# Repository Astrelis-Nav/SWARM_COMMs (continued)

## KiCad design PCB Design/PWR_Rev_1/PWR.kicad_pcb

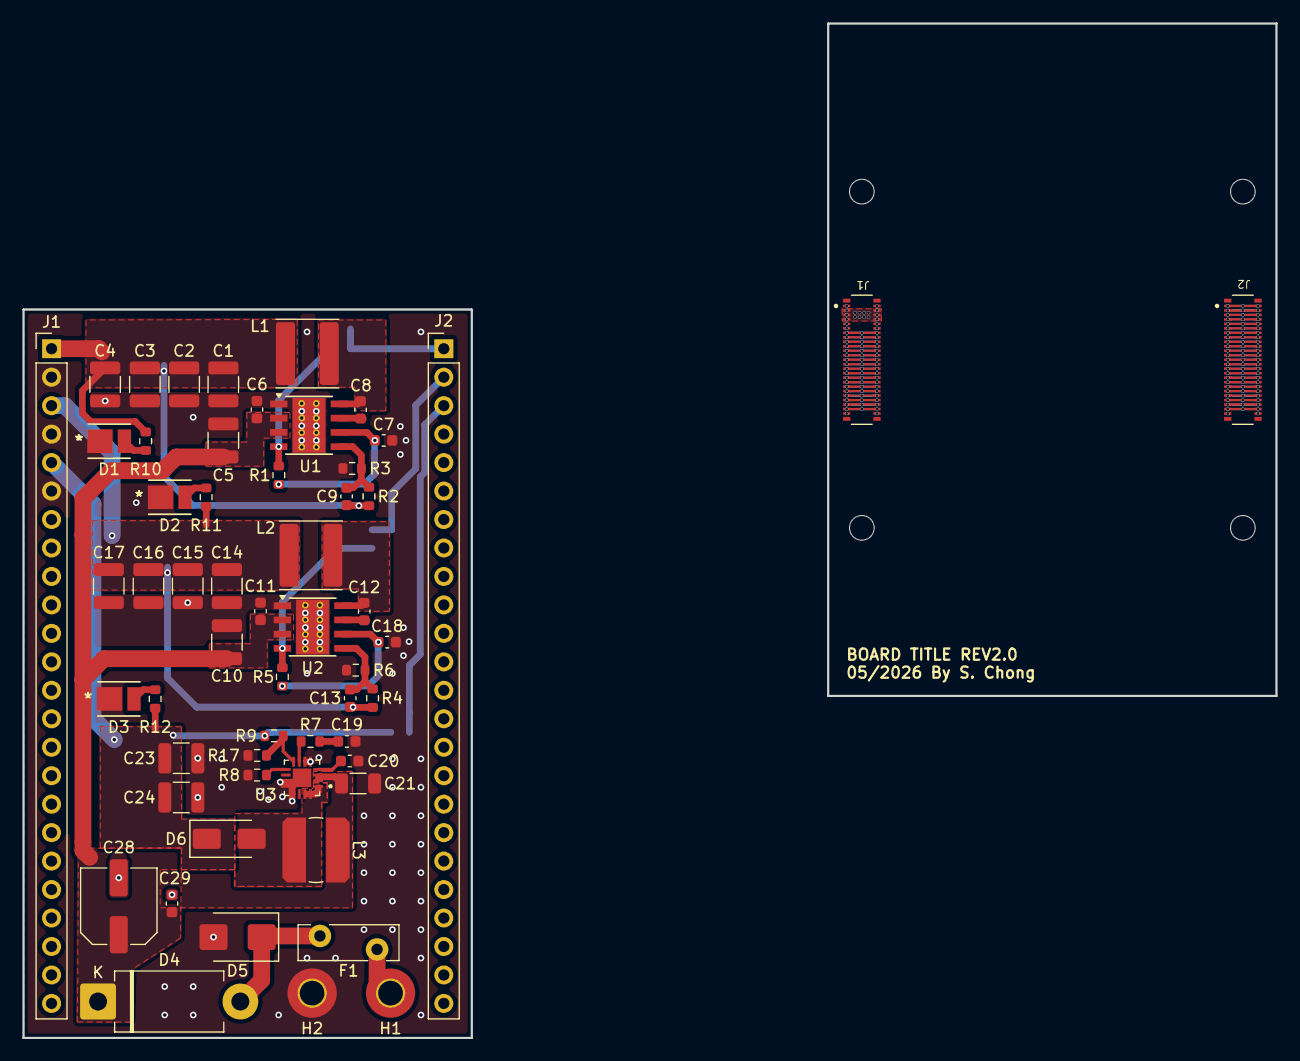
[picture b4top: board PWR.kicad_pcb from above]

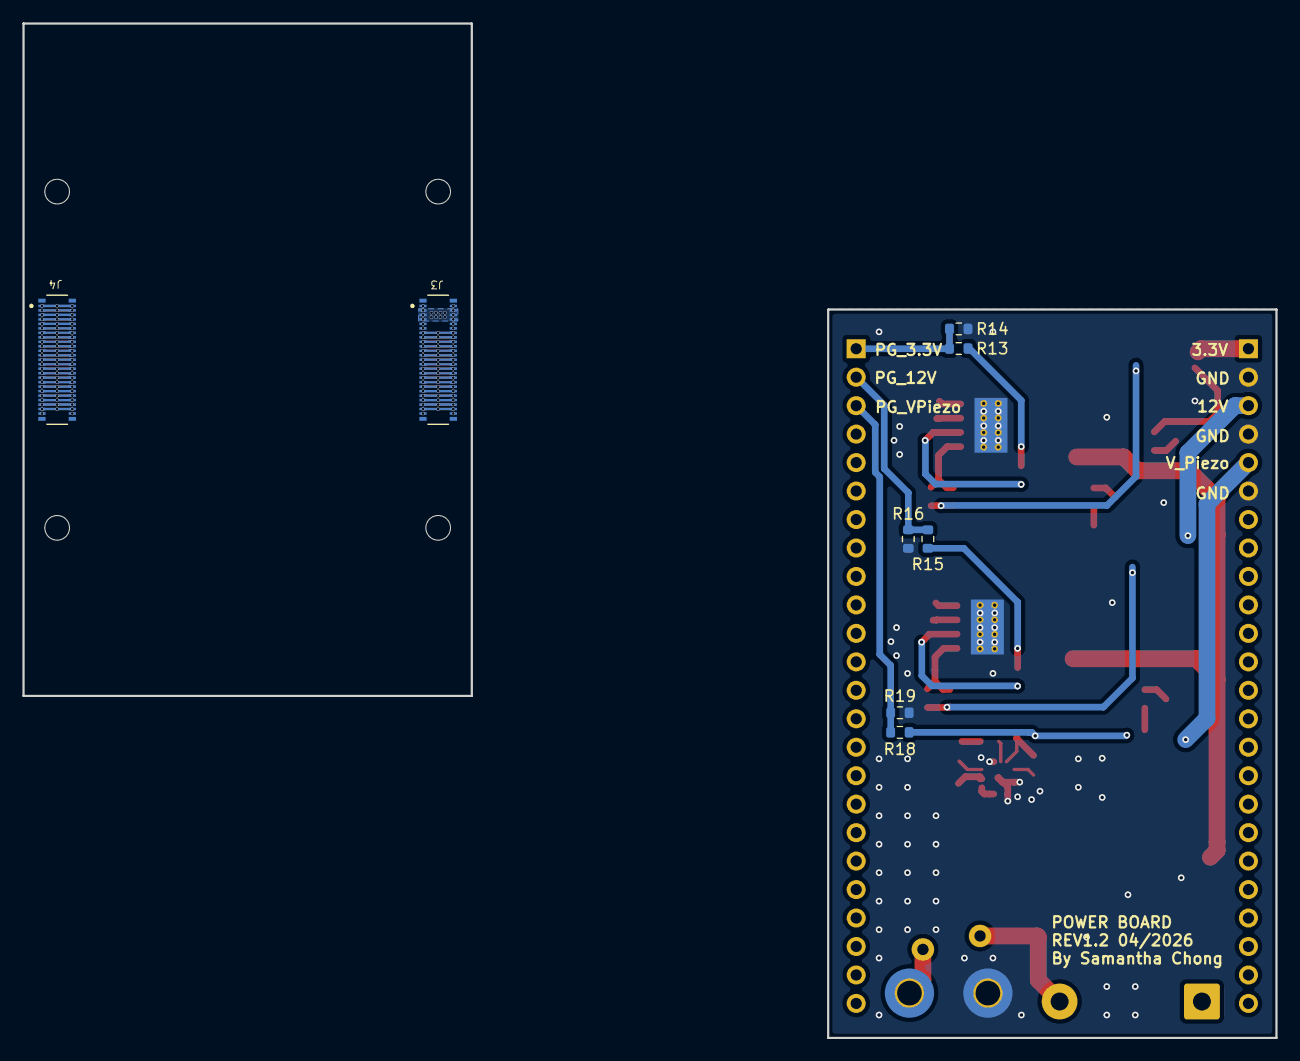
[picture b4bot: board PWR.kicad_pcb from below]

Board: 2 copper layers, 40.0 x 65.0 mm, 65 parts (8 on the bottom side), 71 nets.

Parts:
C1, C2, C3, C4, C14, C15, C16, C17, C23, C24: 22u; C_1210_3225Metric
C5, C10: 10u; C_1210_3225Metric
C6, C11: 0.22u; C_0603_1608Metric
C7, C18: 1u; C_0603_1608Metric
C8, C12: 0.1u; C_0603_1608Metric
C9, C13: C; C_0603_1608Metric
C19: 10n; C_0603_1608Metric
C20: 100n; C_0603_1608Metric
C21: 10u; C_1206_3216Metric
C28: 100uF; C_Elec_6.3x5.8
C29: 2.2uF; C_0603_1608Metric
D1: GREEN; LED_JE2835_CRW
D2, D3: BLUE; LED_JE2835_CRW
D4: STPS5L40; D_DO-201AD_P12.70mm_Horizontal
D5: SMBJ18A; D_SMB
D6: SS34-HF; D_SMA
F1: MF-R300; Fuse_Bourns_MF-RHT300
H1, H2: MountingHole_Pad; MountingHole_2.2mm_M2_Pad_TopBottom
J1, J2, J3, J4: Conn_02x25_Odd_Even; HIROSE_DF40C-50DP-0.4V_51_
J1#2, J2#2: Conn_01x24_Pin; PinHeader_1x24_P2.54mm_Vertical
L1: 6.8u; L_Wuerth_MAPI-5030
L2: 15u; L_Wuerth_MAPI-5030
L3: 22u; L_Bourns_SDR0604
R1, R2, R4, R5, R13, R15: 100k; R_0603_1608Metric
R3: 43.2k; R_0603_1608Metric
R6: 9.09k; R_0603_1608Metric
R7, R17, R19: 10k; R_0603_1608Metric
R8: 84.5k; R_0603_1608Metric
R9: 187k; R_0603_1608Metric
R10: 1k; R_0603_1608Metric
R11: 9.1k; R_0603_1608Metric
R12: R; R_0603_1608Metric
R14, R16: 51k; R_0603_1608Metric
R18: 182k; R_0603_1608Metric
U1, U2: LMR33630ADDA; Texas_HSOP-8-1EP_3.9x4.9mm_P1.27mm_ThermalVias
U3: TPS55340RTER; QFN50P300X300X80-17N

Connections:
3.3V: C1.1, C2.1, C3.1, C4.1, C9.1, J1.3, J1.4, J1.5, J1.6, J1.7, J1.8, J1#2.1, J3.3, J3.4, J3.5, J3.6, J3.7, J3.8, L1.2, R2.2, R10.2
12V: C13.1, C14.1, C15.1, C16.1, C17.1, J1#2.3, L2.2, R4.2, R11.2
+BATT: F1.1, H1.1
/ADC1_IN0: J1.31, J1.32, J3.31, J3.32
/ADC1_IN1: J1.33, J1.34, J3.33, J3.34
/ADC1_IN2: J1.35, J1.36, J3.35, J3.36
/ADC1_IN3: J1.37, J1.38, J3.37, J3.38
/GPIO_6: J1.13, J1.14, J3.13, J3.14
/GPIO_7: J1.15, J1.16, J3.15, J3.16
/GPIO_8: J1.17, J1.18, J3.17, J3.18
/GPIO_9: J1.19, J1.20, J3.19, J3.20
/GPIO_10: J1.21, J1.22, J3.21, J3.22
/GPIO_11: J1.23, J1.24, J3.23, J3.24
/GPIO_12: J1.25, J1.26, J3.25, J3.26
/GPIO_13: J1.27, J1.28, J3.27, J3.28
/GPIO_14: J1.29, J1.30, J3.29, J3.30
/GPIO_16: J2.15, J2.16, J4.15, J4.16
/GPIO_17: J2.13, J2.14, J4.13, J4.14
/GPIO_26: J2.11, J2.12, J4.11, J4.12
/GPIO_27: J2.9, J2.10, J4.9, J4.10
/GPIO_28: J2.7, J2.8, J4.7, J4.8
/HI_A: J1.45, J1.46, J3.45, J3.46
/HI_B: J2.45, J2.46, J4.45, J4.46
/LI_A: J1.47, J1.48, J3.47, J3.48
/LI_B: J2.47, J2.48, J4.47, J4.48
/PA9: J2.33, J2.34, J4.33, J4.34
/PA10: J2.35, J2.36, J4.35, J4.36
/PB0: J1.41, J1.42, J3.41, J3.42
/PB1: J1.43, J1.44, J3.43, J3.44
/PB5: J2.43, J2.44, J4.43, J4.44
/PB6: J2.41, J2.42, J4.41, J4.42
/PB12: J2.19, J2.20, J4.19, J4.20
/PB14: J2.21, J2.22, J4.21, J4.22
/PB15: J2.23, J2.24, J4.23, J4.24
/PC0: J2.3, J2.4, J4.3, J4.4
/PC3: J2.1, J2.2, J4.1, J4.2
/PC4: J2.17, J2.18, J4.17, J4.18
/PC5: J1.39, J1.40, J3.39, J3.40
/PC6: J2.25, J2.26, J4.25, J4.26
/PC7: J2.27, J2.28, J4.27, J4.28
/PC8: J2.29, J2.30, J4.29, J4.30
/PC9: J2.31, J2.32, J4.31, J4.32
/PC13: J2.5, J2.6, J4.5, J4.6
/PG_3.3V: J2#2.1, R13.1, R14.2
/PG_3.3V_IC: R1.1, R13.2, U1.4 (PG)
/PG_12V: J2#2.2, R15.1, R16.2
/PG_12V_IC: R5.1, R15.2, U2.4 (PG)
/PG_VPiezo: J2#2.3, R18.1, R19.2
/SCL: J2.37, J2.38, J4.37, J4.38
/SDA: J2.39, J2.40, J4.39, J4.40
GND: C1.2, C2.2, C3.2, C4.2, C5.2, C6.2, C7.2, C10.2, C11.2, C14.2, C15.2, C16.2, C17.2, C18.2, C19.2, C20.2, C21.2, C23.2, C24.2, C28.2, C29.2, D1.1 (K), D2.1 (K), D3.1 (K), D5.2 (A), H2.1, J1.1, J1.2, J1.9, J1.10, J1.11, J1.12, J1.49, J1.50, J1#2.2, J1#2.4, J1#2.6, J2.49, J2.50, J3.1, J3.2, J3.9, J3.10, J3.11, J3.12, J3.49, J3.50, J4.49, J4.50, R3.1, R6.1, R8.1, R14.1, R16.1, R17.1, R19.1, U1.1 (GND), U1.9 (GND), U2.1 (GND), U2.9 (GND), U3.5 (SYNC), U3.6 (AGND), U3.11 (PGND), U3.12 (PGND), U3.13 (PGND), U3.17 (POWERPAD)
unnamed: C19.1, R7.1
unnamed: D1.2 (A), R10.1
unnamed: D2.2 (A), R11.1
unnamed: D3.2 (A), R12.1
unnamed: D4.2 (A), D5.1 (K), F1.2
unnamed: D6.2 (A), L3.2, U3.1 (SW), U3.15 (SW), U3.16 (SW)
unnamed: C8.2, U1.7 (BOOT)
unnamed: C9.2, R2.1, R3.2, U1.5 (FB)
unnamed: C8.1, L1.1, U1.8 (SW)
unnamed: C7.1, R1.2, U1.6 (VCC)
unnamed: C12.2, U2.7 (BOOT)
unnamed: C13.2, R4.1, R6.2, U2.5 (FB)
unnamed: C12.1, L2.1, U2.8 (SW)
unnamed: C18.1, R5.2, U2.6 (VCC)
unnamed: R7.2, U3.7 (COMP)
unnamed: R9.1, R17.2, U3.8 (FB)
unnamed: R8.2, U3.9 (FREQ)
unnamed: C20.1, U3.4 (SS)
VIN: C5.1, C6.1, C10.1, C11.1, C21.1, C28.1, C29.1, D4.1 (K), L3.1, U1.2 (VIN), U1.3 (EN), U2.2 (VIN), U2.3 (EN), U3.2 (VIN), U3.3 (EN)
V_Piezo: C23.1, C24.1, D6.1 (K), J1#2.5, R9.2, R12.2, R18.2

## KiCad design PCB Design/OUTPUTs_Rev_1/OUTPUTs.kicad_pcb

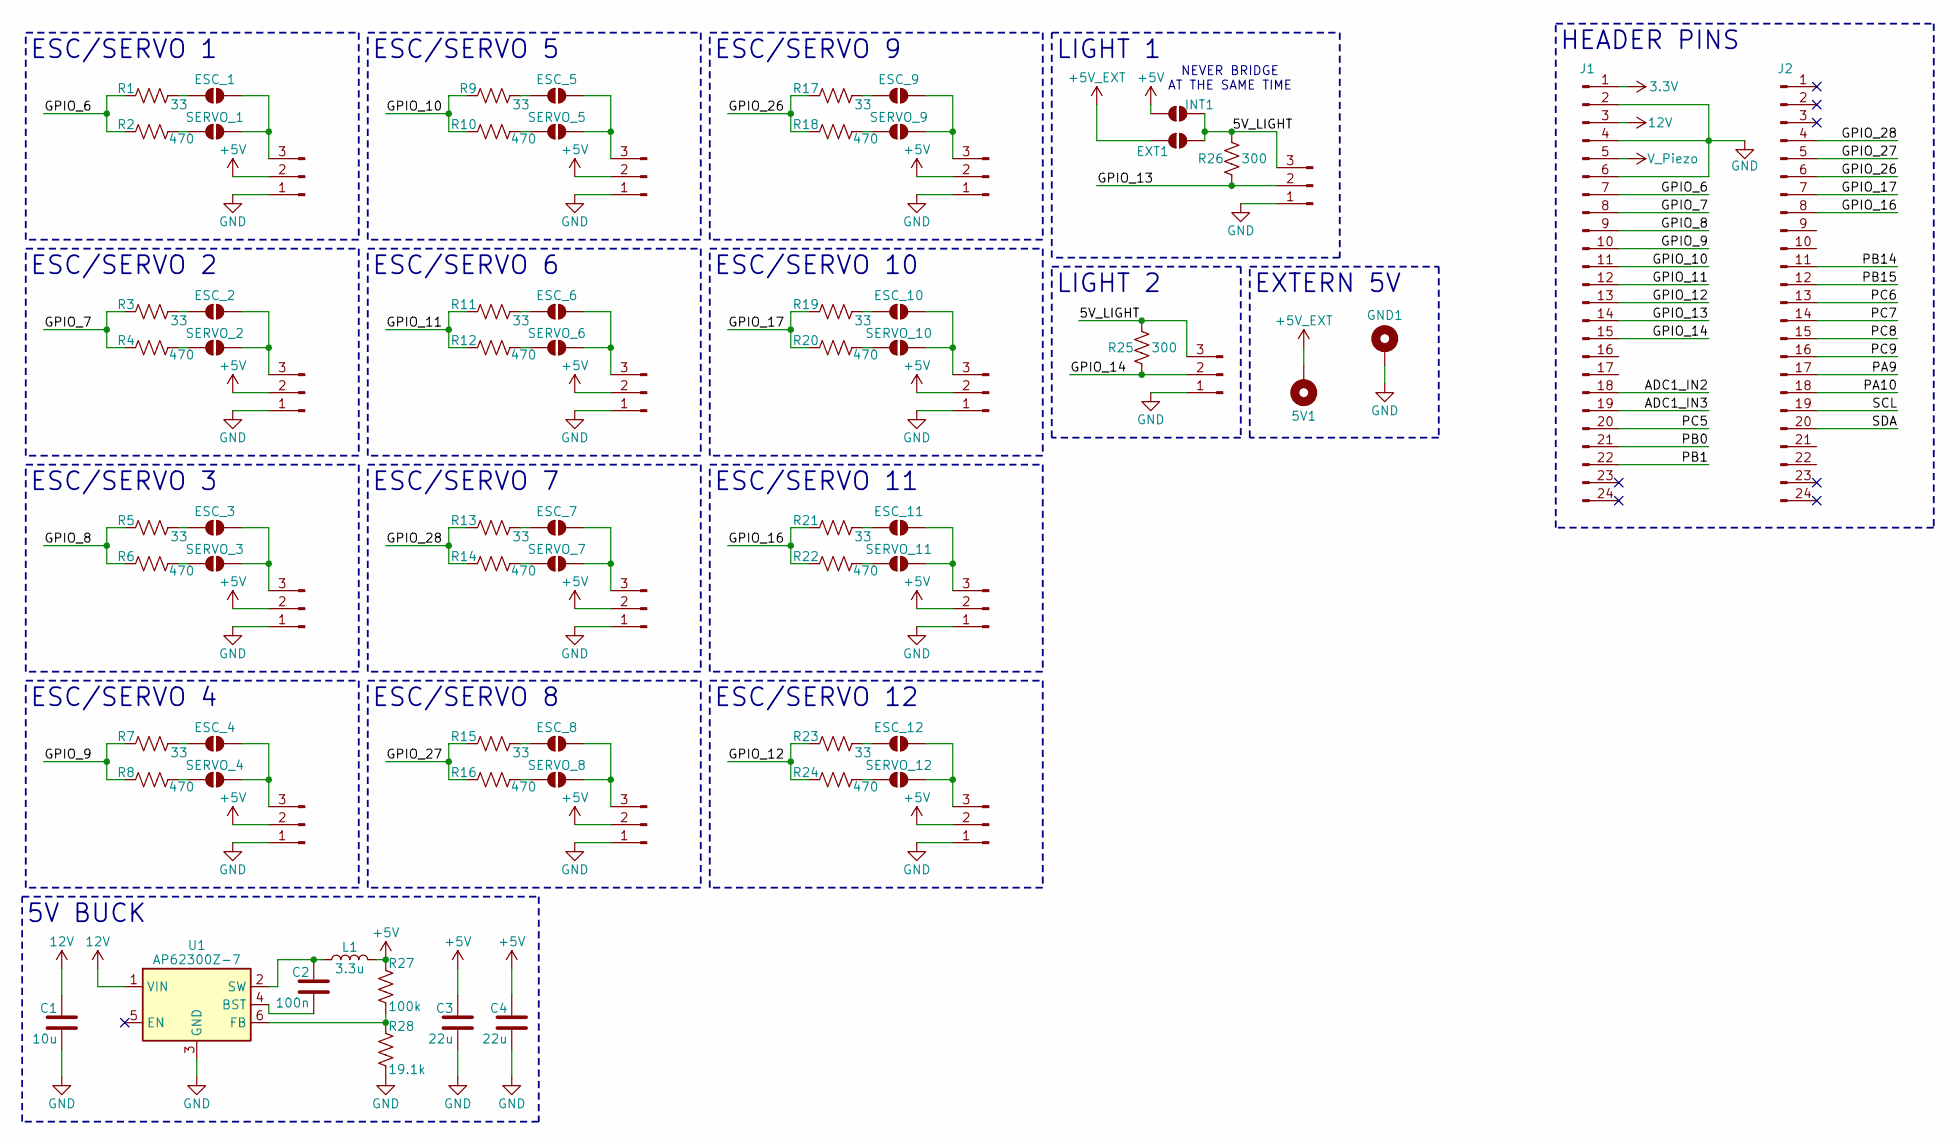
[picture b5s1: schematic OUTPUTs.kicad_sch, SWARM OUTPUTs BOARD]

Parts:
5V1: MountingHole_Pad; MountingHole_2.2mm_M2_Pad_Via
C1: 10u; C_0603_1608Metric
C2: 100n; C_0603_1608Metric
C3, C4: 22u; C_0603_1608Metric
ESC_1, ESC_2, ESC_3, ESC_4, ESC_5, ESC_6, ESC_7, ESC_8, ESC_9, ESC_10, ESC_11, ESC_12: SolderJumper_2_Open; SolderJumper-2_P1.3mm_Open_TrianglePad1.0x1.5mm
EXT1: SolderJumper_2_Open; SolderJumper-2_P1.3mm_Open_TrianglePad1.0x1.5mm
GND1: MountingHole_Pad; MountingHole_2.2mm_M2_Pad_Via
INT1: SolderJumper_2_Open; SolderJumper-2_P1.3mm_Open_TrianglePad1.0x1.5mm
J1, J2: Conn_01x24_Pin; PinHeader_1x24_P2.54mm_Vertical
L1: 3.3u; L_1008_2520Metric
LIGHT_1, LIGHT_2: Conn_01x03_Pin; PinHeader_1x03_P2.54mm_Vertical
OUT_1, OUT_2, OUT_3, OUT_4, OUT_5, OUT_6, OUT_7, OUT_8, OUT_9, OUT_10, OUT_11, OUT_12: Conn_01x03_Pin; PinHeader_1x03_P2.54mm_Vertical
R1, R3, R5, R7, R9, R11, R13, R15, R17, R19, R21, R23: 33; R_0603_1608Metric
R2, R4, R6, R8, R10, R12, R14, R16, R18, R20, R22, R24: 470; R_0603_1608Metric
R25, R26: 300; R_0603_1608Metric
R27: 100k; R_0603_1608Metric
R28: 19.1k; R_0603_1608Metric
SERVO_1, SERVO_2, SERVO_3, SERVO_4, SERVO_5, SERVO_6, SERVO_7, SERVO_8, SERVO_9, SERVO_10, SERVO_11, SERVO_12: SolderJumper_2_Open; SolderJumper-2_P1.3mm_Open_TrianglePad1.0x1.5mm
U1: AP62300Z-7; SOT-563

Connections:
3.3V: J1.1
12V: C1.1, J1.3, U1.1 (VIN)
+5V: C3.1, C4.1, INT1.1 (A), L1.2, OUT_1.2, OUT_2.2, OUT_3.2, OUT_4.2, OUT_5.2, OUT_6.2, OUT_7.2, OUT_8.2, OUT_9.2, OUT_10.2, OUT_11.2, OUT_12.2, R27.2
+5V_EXT: 5V1.1, EXT1.1 (A)
/5V_LIGHT: EXT1.2 (B), INT1.2 (B), LIGHT_1.3, LIGHT_2.3, R25.2, R26.2
/ADC1_IN2: J1.18
/ADC1_IN3: J1.19
/GPIO_6: J1.7, R1.1, R2.1
/GPIO_7: J1.8, R3.1, R4.1
/GPIO_8: J1.9, R5.1, R6.1
/GPIO_9: J1.10, R7.1, R8.1
/GPIO_10: J1.11, R9.1, R10.1
/GPIO_11: J1.12, R11.1, R12.1
/GPIO_12: J1.13, R23.1, R24.1
/GPIO_13: J1.14, LIGHT_2.2, R26.1
/GPIO_14: J1.15, LIGHT_1.2, R25.1
/GPIO_16: J2.8, R21.1, R22.1
/GPIO_17: J2.7, R19.1, R20.1
/GPIO_26: J2.6, R17.1, R18.1
/GPIO_27: J2.5, R15.1, R16.1
/GPIO_28: J2.4, R13.1, R14.1
/PA9: J2.17
/PA10: J2.18
/PB0: J1.21
/PB1: J1.22
/PB14: J2.11
/PB15: J2.12
/PC5: J1.20
/PC6: J2.13
/PC7: J2.14
/PC8: J2.15
/PC9: J2.16
/SCL: J2.19
/SDA: J2.20
GND: C1.2, C3.2, C4.2, GND1.1, J1.2, J1.4, J1.6, LIGHT_1.1, LIGHT_2.1, OUT_1.1, OUT_2.1, OUT_3.1, OUT_4.1, OUT_5.1, OUT_6.1, OUT_7.1, OUT_8.1, OUT_9.1, OUT_10.1, OUT_11.1, OUT_12.1, R28.1, U1.3 (GND)
unnamed: ESC_1.1 (A), R1.2
unnamed: ESC_1.2 (B), OUT_1.3, SERVO_1.2 (B)
unnamed: ESC_2.1 (A), R3.2
unnamed: ESC_2.2 (B), OUT_2.3, SERVO_2.2 (B)
unnamed: ESC_3.1 (A), R5.2
unnamed: ESC_3.2 (B), OUT_3.3, SERVO_3.2 (B)
unnamed: ESC_4.1 (A), R7.2
unnamed: ESC_4.2 (B), OUT_4.3, SERVO_4.2 (B)
unnamed: ESC_5.1 (A), R9.2
unnamed: ESC_5.2 (B), OUT_5.3, SERVO_5.2 (B)
unnamed: ESC_6.1 (A), R11.2
unnamed: ESC_6.2 (B), OUT_6.3, SERVO_6.2 (B)
unnamed: ESC_7.1 (A), R13.2
unnamed: ESC_7.2 (B), OUT_7.3, SERVO_7.2 (B)
unnamed: ESC_8.1 (A), R15.2
unnamed: ESC_8.2 (B), OUT_8.3, SERVO_8.2 (B)
unnamed: ESC_9.1 (A), R17.2
unnamed: ESC_9.2 (B), OUT_9.3, SERVO_9.2 (B)
unnamed: ESC_10.1 (A), R19.2
unnamed: ESC_10.2 (B), OUT_10.3, SERVO_10.2 (B)
unnamed: ESC_11.1 (A), R21.2
unnamed: ESC_11.2 (B), OUT_11.3, SERVO_11.2 (B)
unnamed: ESC_12.1 (A), R23.2
unnamed: ESC_12.2 (B), OUT_12.3, SERVO_12.2 (B)
unnamed: R2.2, SERVO_1.1 (A)
unnamed: R4.2, SERVO_2.1 (A)
unnamed: R6.2, SERVO_3.1 (A)
unnamed: R8.2, SERVO_4.1 (A)
unnamed: R10.2, SERVO_5.1 (A)
unnamed: R12.2, SERVO_6.1 (A)
unnamed: R14.2, SERVO_7.1 (A)
unnamed: R16.2, SERVO_8.1 (A)
unnamed: R18.2, SERVO_9.1 (A)
unnamed: R20.2, SERVO_10.1 (A)
unnamed: R22.2, SERVO_11.1 (A)
unnamed: R24.2, SERVO_12.1 (A)
unnamed: C2.2, U1.4 (BST)
unnamed: R27.1, R28.2, U1.6 (FB)
unnamed: C2.1, L1.1, U1.2 (SW)
V_Piezo: J1.5

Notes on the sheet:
ESC/SERVO 12
EXTERN 5V
ESC/SERVO 11
5V BUCK
ESC/SERVO 8
ESC/SERVO 3
LIGHT 2
ESC/SERVO 2
ESC/SERVO 1
HEADER PINS
ESC/SERVO 5
NEVER BRIDGE AT THE SAME TIME
ESC/SERVO 4
ESC/SERVO 7
ESC/SERVO 9
ESC/SERVO 10
LIGHT 1
ESC/SERVO 6

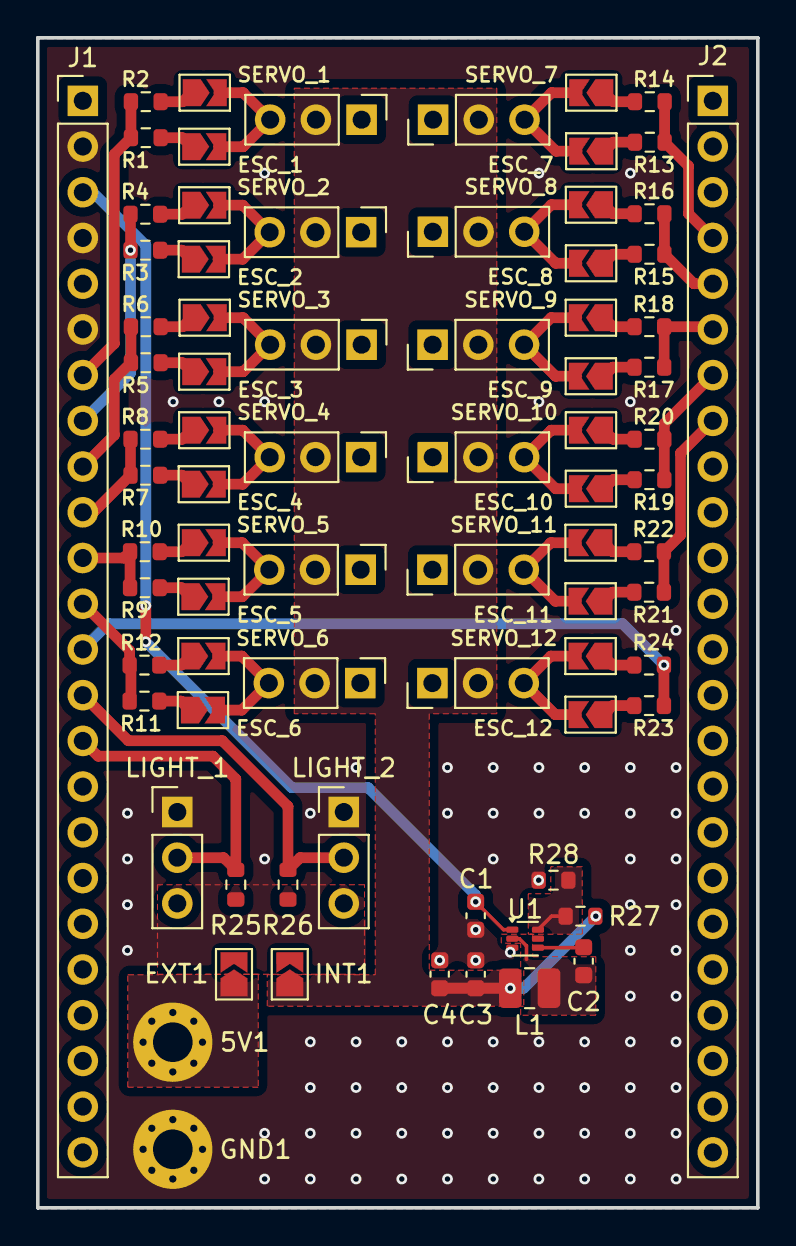
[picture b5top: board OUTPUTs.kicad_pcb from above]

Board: 2 copper layers, 40.0 x 65.0 mm, 78 parts (0 on the bottom side), 58 nets.

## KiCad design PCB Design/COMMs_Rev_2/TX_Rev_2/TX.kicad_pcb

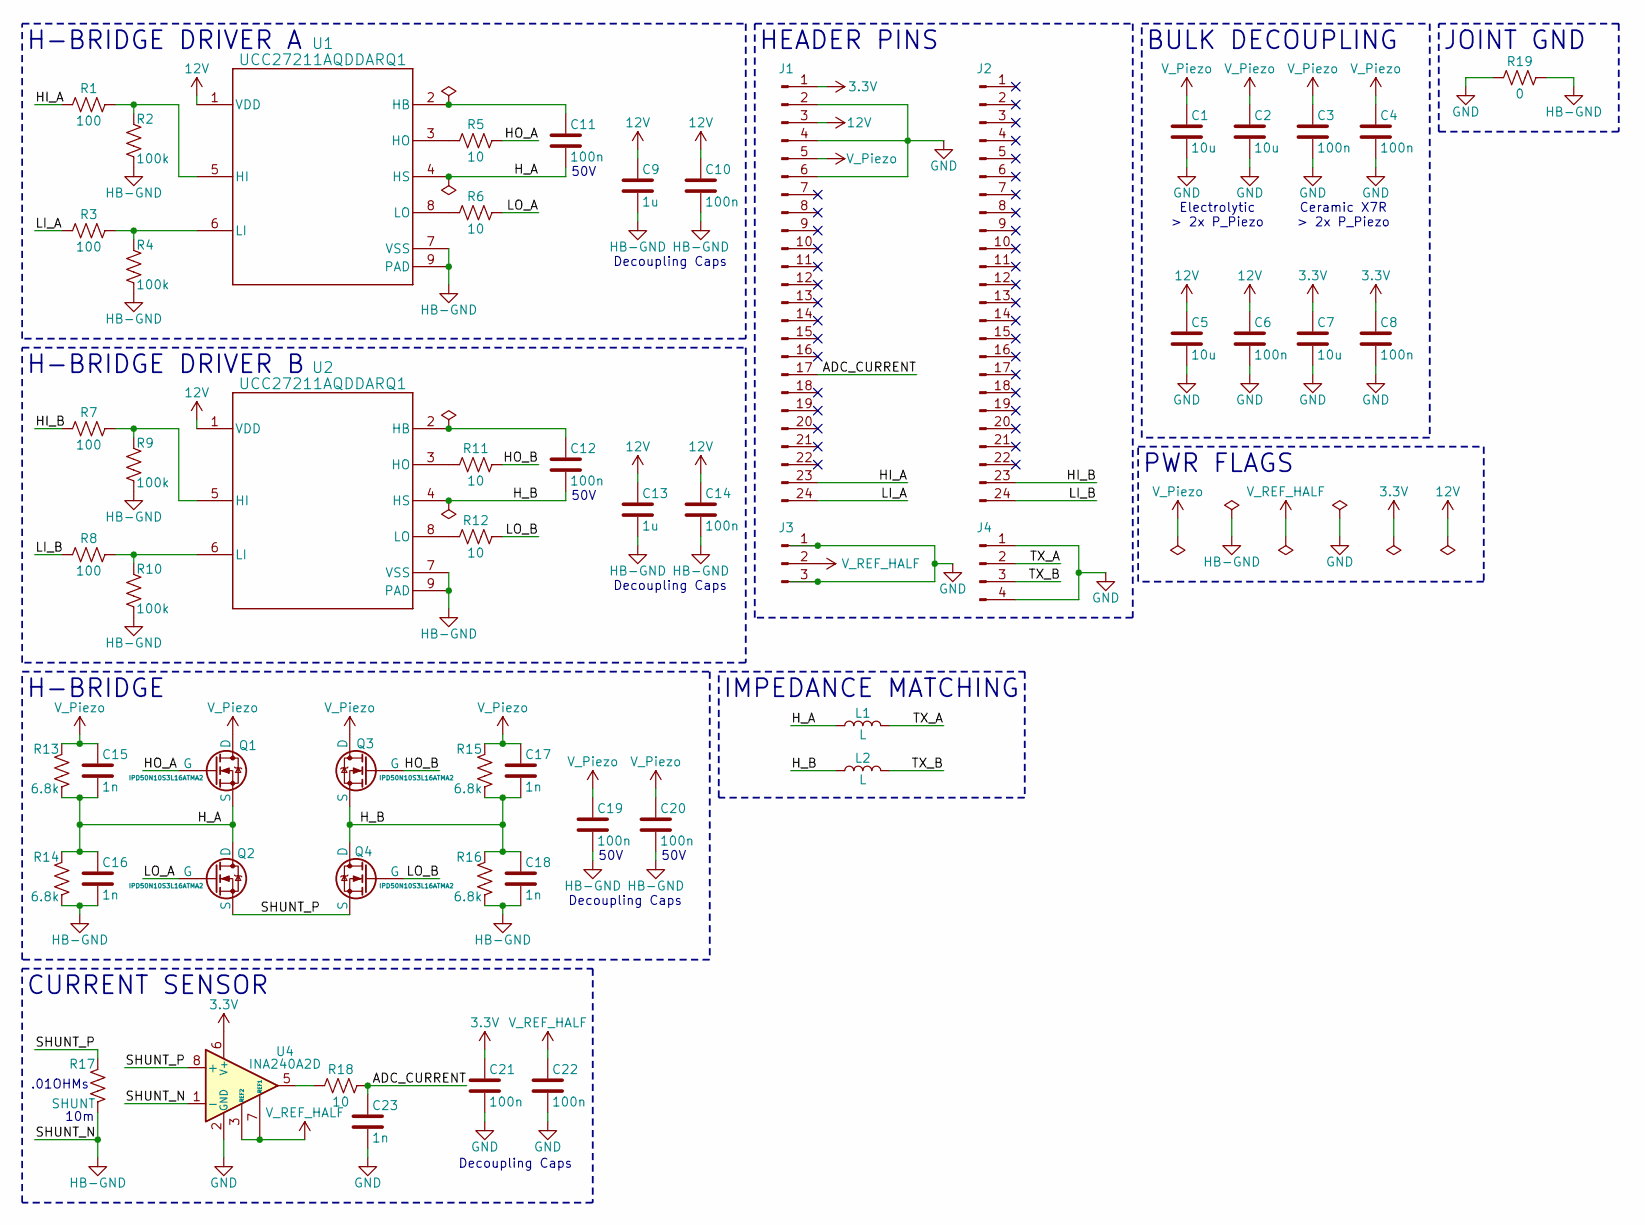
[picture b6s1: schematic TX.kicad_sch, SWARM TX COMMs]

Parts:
C1, C2, C5, C7: 10u; C_1206_3216Metric
C3, C4, C6, C8, C10, C11, C12, C14, C19, C20, C21, C22: 100n; C_0603_1608Metric
C9, C13: 1u; C_0603_1608Metric
C15, C16, C17, C18, C23: 1n; C_0603_1608Metric
J1, J2: Conn_01x24_Pin; PinHeader_1x24_P2.54mm_Vertical
J3: Conn_01x03_Pin; PinHeader_1x03_P2.54mm_Vertical
J4: Conn_01x04_Pin; PinHeader_1x04_P2.54mm_Vertical
L1, L2: L; L_Wuerth_MAPI-5030
Q1, Q2, Q3, Q4: IPD50N10S3L16ATMA2; TO-252-3_TabPin2
R1, R3, R7, R8: 100; R_0603_1608Metric
R2, R4, R9, R10: 100k; R_0603_1608Metric
R5, R6, R11, R12, R18: 10; R_0603_1608Metric
R13, R14, R15, R16: 6.8k; R_0603_1608Metric
R17: SHUNT; R_2512_6332Metric
R19: 0; R_0603_1608Metric
U1, U2: UCC27211AQDDARQ1; DDA0008E_L
U4: INA240A2D; SOIC-8_3.9x4.9mm_P1.27mm

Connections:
3.3V: C7.1, C8.1, C21.1, J1.1, U4.6 (V+)
12V: C5.1, C6.1, C9.1, C10.1, C13.1, C14.1, J1.3, U1.1 (VDD), U2.1 (VDD)
/ADC_CURRENT: C23.1, J1.17, R18.2
/HI_A: J1.23, R1.1
/HI_B: J2.23, R7.1
/HO_A: Q1.2 (G), R5.2
/HO_B: Q3.2 (G), R11.2
/H_A: C11.2, C15.2, C16.1, L1.1, Q1.3 (S), Q2.1 (D), R13.2, R14.1, U1.4 (HS)
/H_B: C12.2, C17.2, C18.1, L2.1, Q3.3 (S), Q4.1 (D), R15.2, R16.1, U2.4 (HS)
/LI_A: J1.24, R3.1
/LI_B: J2.24, R8.1
/LO_A: Q2.2 (G), R6.2
/LO_B: Q4.2 (G), R12.2
/SHUNT_P: Q2.3 (S), Q4.3 (S), R17.1, U4.8 (+)
/TX_A: J4.2, L1.2
/TX_B: J4.3, L2.2
GND: C1.2, C2.2, C3.2, C4.2, C5.2, C6.2, C7.2, C8.2, C21.2, C22.2, C23.2, J1.2, J1.4, J1.6, J3.1, J3.3, J4.1, J4.4, R19.1, U4.2 (GND), U4.4 (GND)
HB-GND: C9.2, C10.2, C13.2, C14.2, C16.2, C18.2, C19.2, C20.2, R2.2, R4.2, R9.2, R10.2, R14.2, R16.2, R17.2, R19.2, U1.7 (VSS), U1.9 (PAD), U2.7 (VSS), U2.9 (PAD), U4.1 (-)
unnamed: R18.1, U4.5
unnamed: C11.1, U1.2 (HB)
unnamed: R1.2, R2.1, U1.5 (HI)
unnamed: R5.1, U1.3 (HO)
unnamed: R3.2, R4.1, U1.6 (LI)
unnamed: R6.1, U1.8 (LO)
unnamed: C12.1, U2.2 (HB)
unnamed: R7.2, R9.1, U2.5 (HI)
unnamed: R11.1, U2.3 (HO)
unnamed: R8.2, R10.1, U2.6 (LI)
unnamed: R12.1, U2.8 (LO)
V_Piezo: C1.1, C2.1, C3.1, C4.1, C15.1, C17.1, C19.1, C20.1, J1.5, Q1.1 (D), Q3.1 (D), R13.1, R15.1
V_REF_HALF: C22.1, J3.2, U4.3 (REF2), U4.7 (REF1)

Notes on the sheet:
50V
Decoupling Caps
.01OHMs
Electrolytic > 2x P_Piezo
PWR FLAGS
10m
H-BRIDGE
H-BRIDGE DRIVER A
IMPEDANCE MATCHING
BULK DECOUPLING
JOINT GND
CURRENT SENSOR
HEADER PINS
H-BRIDGE DRIVER B
Ceramic X7R > 2x P_Piezo

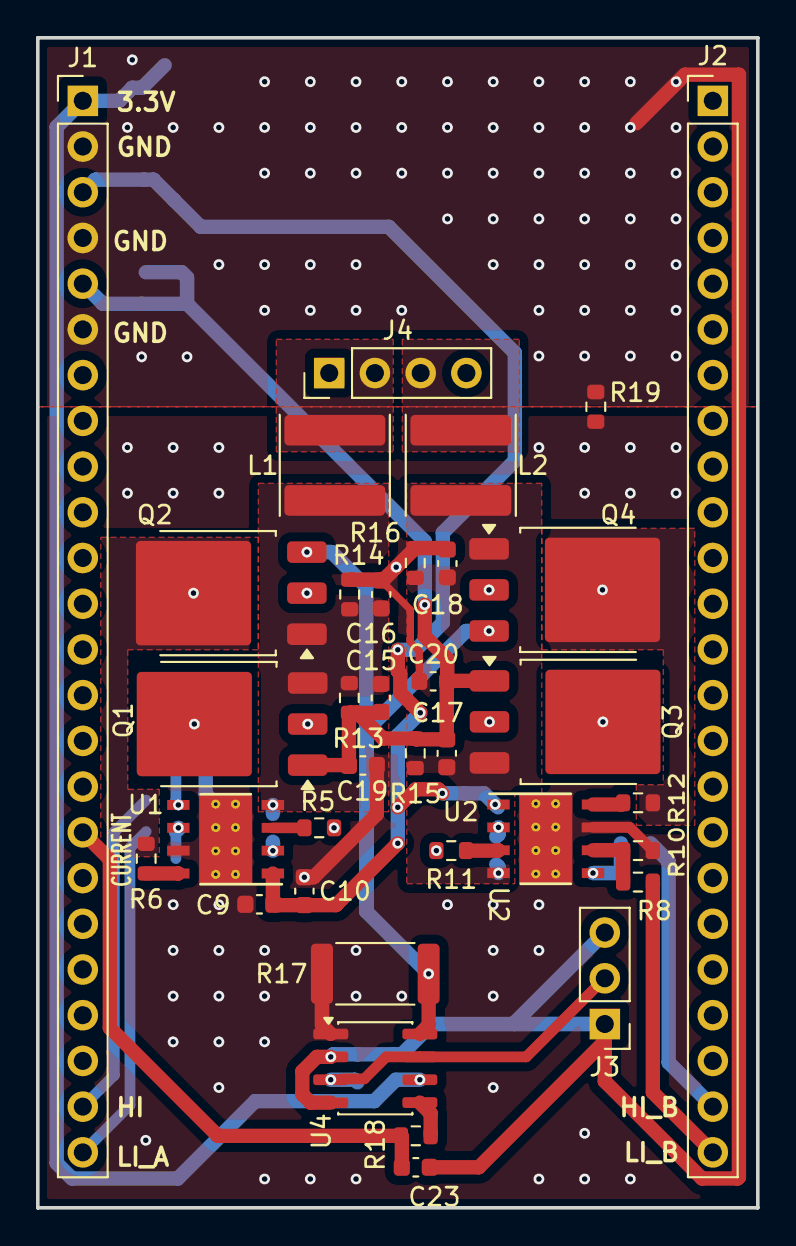
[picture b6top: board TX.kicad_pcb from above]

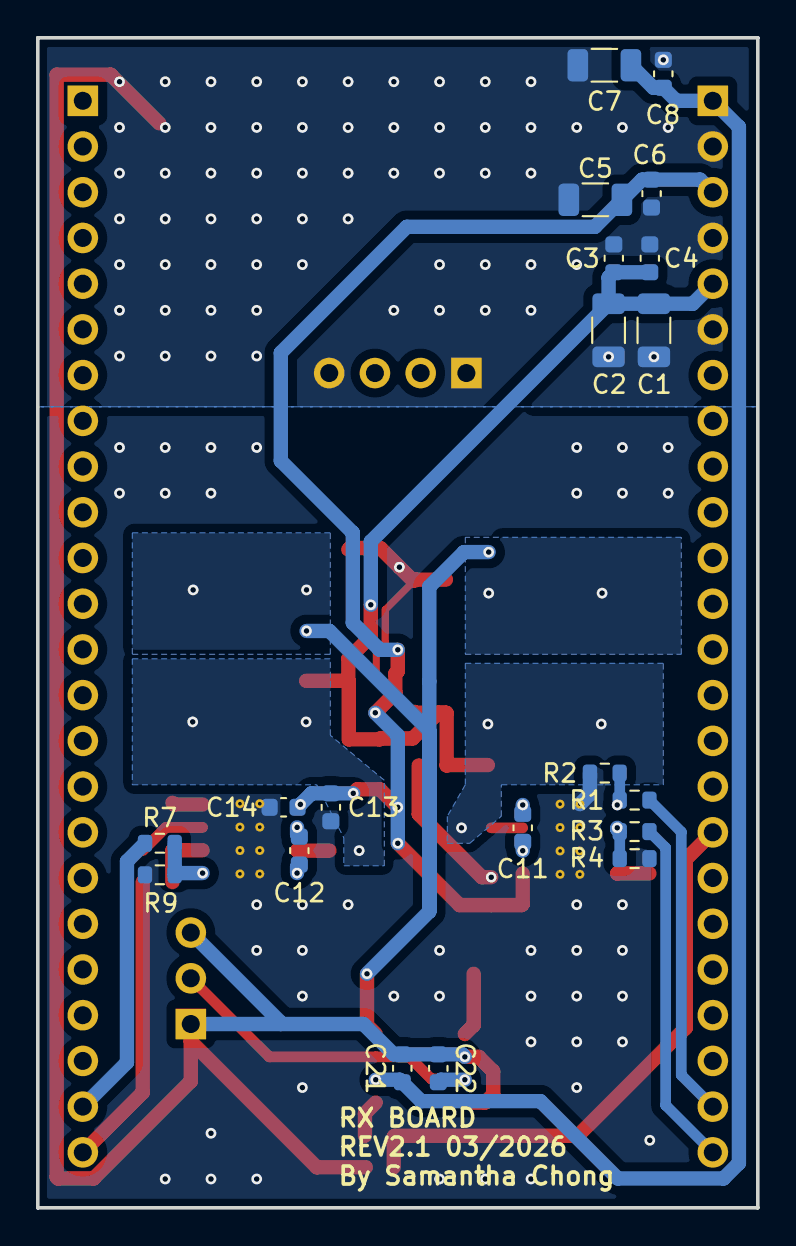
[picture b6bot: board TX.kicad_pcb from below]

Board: 2 copper layers, 40.0 x 65.0 mm, 55 parts (20 on the bottom side), 31 nets.

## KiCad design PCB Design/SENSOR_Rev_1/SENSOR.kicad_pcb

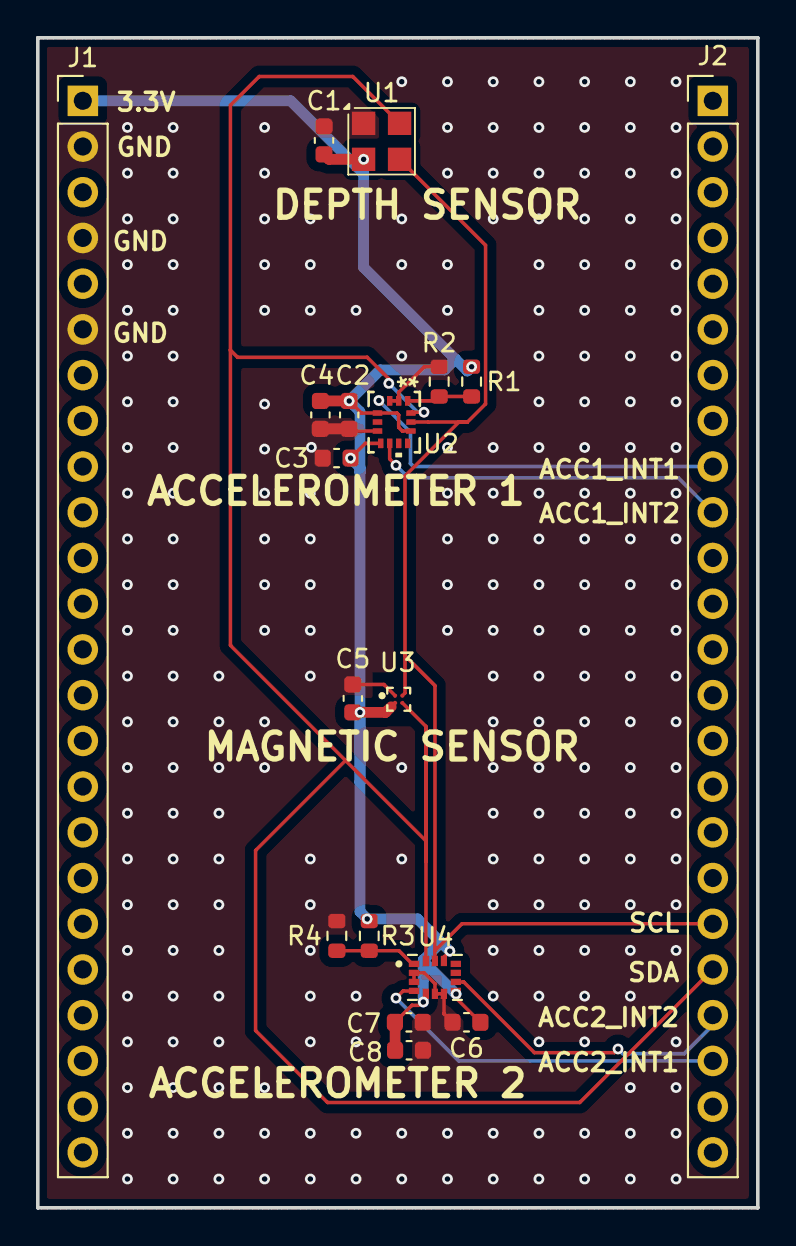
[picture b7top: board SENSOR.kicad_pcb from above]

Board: 2 copper layers, 40.0 x 65.0 mm, 18 parts (0 on the bottom side), 10 nets.

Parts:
C1, C2, C3, C6, C7: 100n; C_0603_1608Metric
C4, C8: 10u; C_0603_1608Metric
C5: 2.2u; C_0603_1608Metric
J1, J2: Conn_01x24_Pin; PinHeader_1x24_P2.54mm_Vertical
R1, R2, R3, R4: 0; R_0603_1608Metric
U1: MS583730BA01-50; TE_MS5837-xxBA
U2: ASM330LHHXG1TR; LGA14_2P5X3_STM
U3: MMC5603NJ; XDCR_MMC5603NJ
U4: LSM6DSO32TR; XDCR_LSM6DSO32TR

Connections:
3.3V: C1.1, C2.1, C3.1, C4.1, C5.1, C6.1, C7.1, C8.1, J1.1, R1.2, R3.2, U1.2 (VDD), U2.5 (VDD_IO), U2.8 (VDD_IO), U2.12 (CS), U3.B1 (VDD), U4.5 (VDDIO), U4.8 (VDD), U4.12 (CS)
/ACC1_ADD: R1.1, R2.1, U2.1 (SDO/SA0)
/ACC1_INT1: J2.9, U2.4 (INT1)
/ACC1_INT2: J2.10, U2.9 (INT2)
/ACC2_ADD: R3.1, R4.1, U4.1 (SDO/SA0)
/ACC2_INT1: J2.22, U4.4 (INT1)
/ACC2_INT2: J2.21, U4.9 (INT2)
/SCL: J2.19, U1.3 (SCL), U2.13 (SCL), U3.A2 (SCL), U4.13 (SCL)
/SDA: J2.20, U1.4 (SDA), U2.14 (SDA), U3.B2 (SDA), U4.14 (SDA)
GND: C1.2, C2.2, C3.2, C4.2, C5.2, C6.2, C7.2, C8.2, J1.2, J1.4, J1.6, R2.2, R4.2, U1.1 (GND), U2.2 (MSDA), U2.3 (MSCL), U2.7 (GND), U3.A1 (VSA), U4.2 (SDX), U4.3 (SCX), U4.6 (GND), U4.7 (GND)

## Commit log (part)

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2026-02-10 Added V1 Board
2026-03-09 Updated COMMs Board
2026-03-09 Started CONTROL Board
2026-03-09 Designed PWR Board
    Designed and exported PWR Board (sent to manufacture)
2026-03-09 Initial Component Layout of Main MCU
2026-03-11 Finished Schematic, Started Placing Components on PCB
2026-03-16 Cleaned up Formating
    Cleaned up formatting and added required exports for delivery
2026-03-16 Minor Schematic Updates and PCB Routing
2026-03-18 Completed Rev1 and Documentation
2026-03-18 Zipped Output File
2026-03-18 Minor Fixes
2026-03-18 Created Sensor Board
2026-03-19 Added Sensor Names to Silkscreen
2026-03-20 Updated Sensor Output Files
2026-03-20 Small Updates
2026-03-21 Fixed Schematic Errors
2026-03-21 RX Initial Schematic Design
2026-03-22 Removed Out of Date Files
2026-03-22 Updated Sensor to new Version
2026-03-22 Claude PCB Review
    Made updates based on Claude's Review
    - Added decoupling capacitor
    - Verified CS pins
    - Compared placement and connections to data sheets
2026-03-22 Claude Design Review
    fix: tie ASM330 MSCL/MSDA to GND; DNP mark address jumpers R1/R3
2026-03-22 Update SENSOR.kicad_pcb
    fix: add copper pour keepout under MMC5603NJ (U3)
2026-03-22 Added Sensor Board Exports
2026-03-22 fix(usb-c): add ESD protection and clean up VBUS handling
    - Add USBLC6-2SC6 TVS diode array on D+ and D- (J4)
    - Add 100k bleed resistor from VBUS to GND (VBUS not powered)
2026-03-22 Updated USB Port Schematic and PCB
2026-03-22 fix(sd-card): pull up unused DAT1 and DAT2 lines
    - Add 47k pull-up resistors on DAT1 (pin 8) and DAT2 (pin 1) to 3.3V
    - Required by SD spec to prevent undefined bus state during init
2026-03-22 fix(crystals): correct LSE load cap configuration
    - Remove C13 and C14 (1.2pF external load caps on LSE)
    - ABS05W has CL = 4pF; use STM32 internal OSC caps instead
    - HSE caps C11/C12 confirmed correct at 10pF for E3SB16E (CL = 8pF)
    - Note: configure LSE drive to low-power mode in firmware to match ABS05W ESR
2026-03-22 fix(pico): connect power pins and add reset pull-up
    - Connect VSYS (pin 39) to 3.3V rail via header
    - Connect 3V3_EN (pin 37) to 3.3V to keep regulator enabled
    - Add 10k pull-up resistor on RUN (pin 30) to 3.3V
    - Add no-connect on 3V3 (pin 36) — Pico regulator output unused
    - Add no-connect on VBUS (pin 40) — USB power not used
2026-03-22 fix(uart): correct inter-MCU UART cross-connection
    - Swap UART net labels on Pico side to correctly cross TX/RX
    - Pico GPIO4 (pin 6): UART_TX -> UART_RX (connects to STM32 PA9/USART1_TX)
    - Pico GPIO5 (pin 7): UART_RX -> UART_TX (connects to STM32 PA10/USART1_RX)
    - Both MCUs confirmed on 3.3V — no level shifting required
2026-03-22 fix(layout): move HSE and LSE crystals closer to STM32 OSC pins
    - Relocate Y1 (16MHz HSE) directly above STM32 to reduce trace length
    - Relocate Y2 (32.768kHz LSE) alongside Y1 above STM32
    - C11/C12 load caps repositioned to follow crystals
    - Shorter direct traces to PH0/PH1 and PC14/PC15 OSC pins
2026-03-22 Added Control Board Outputs
2026-03-23 Initial PCB Placement
2026-03-23 Completed Initial PCB Component Placements
2026-03-23 RX_Rev_2 schematic design review fixes
    - Set R14 gain resistor to calculated value for target INA828 gain
    - Resolved C6 ambiguity (marked DNP)
2026-03-23 Update TX.kicad_sch
    R5, R6, R11, R12: 3.3Ω → 10Ω (gate resistors)
    R17: SHUNT → 0.01 (10mΩ shunt, 2512 footprint already correct)
2026-03-23 Added PWR Export Files
2026-03-23 Added Title Summary and Updated Rev 2.1
2026-03-23 Updated Revision Number and Title Block
2026-03-23 Updated Schematic to include Inductor Matching Inductors
2026-03-23 Updated MOSFET
2026-03-23 Generated TX Board Outputs
2026-03-23 RX Board Outputs
2026-03-24 Fixed Incorrect Revision Numbers
2026-03-30 PWR - Updated 3D Models for Full Board Export
2026-03-30 SENSOR - Added and Exported 3D Model of PCB
2026-03-30 CONTROL - Added 3D Models for Export
2026-03-30 RX Added 3D Model and Export
2026-03-30 TX 3D Models and Export
2026-04-15 Added Voltage Divider
    Added Voltage Divider to 3.3PG and 12VPG
2026-04-15 Moved Rev 1.1 to Archive
2026-04-15 PWR Rev 1.2 Exports
2026-04-15 Added Boost for V_Piezo
2026-04-15 Fixed Typoed Date
2026-04-15 Moved COMMs Rev 1 to Achive
2026-04-16 Created OUTPUTs Board
2026-04-30 Updated RX
2026-04-30 Updated to KiCAD 10 and exported BOM
2026-05-19 Revert "Updated"
    This reverts commit 89be44ed720659141c8ee702c54a520a60db740f.
2026-05-20 Created Rev 2 Project
    Rev 2 project files with all boards under one project
2026-05-20 CONTROL Schematic Rev2
2026-05-20 HEADER PINS Schematic
2026-05-20 Made Rev 2 Sensor Schematic
2026-05-20 Component Library
2026-05-21 Created Power Schematic
2026-05-21 Additional Footprints
2026-05-25 Reannotated Schematic
2026-05-26 Finished Placement for POWER, CONTROL and SENSOR
2026-05-26 TX Board Schematic
2026-06-08 Completed PCB Layout
2026-06-15 Fixed DRC and ERC errors
2026-06-16 Fixed Via size and added Copper Pours for POWER BOARD
2026-06-16 Trace Tuning
2026-06-18 Fixed some small errors and added the Output board
2026-06-19 Resolved all DRC and ERC errors
2026-06-19 to delete
2026-06-19 Completed Panalization
2026-06-19 Revert "to delete"
    This reverts commit 543c70bcba01ecf78262208d4f10808184dfb0ad.
2026-06-19 Finalized Design of Rev 2.1 and fixed all ERC and DRC errors
2026-06-19 Generated Output Files
2026-06-22 Updated Via size to 0.25mm and ReExported Files
2026-06-22 Cleaned up the files
2026-06-25 Cleaned up Schematic and Exported
